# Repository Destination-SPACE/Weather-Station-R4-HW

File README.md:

# Destination Weather Station R4 - Hardware
Hardware repository for the Destination Weather Station R4 remote sensing platform

## Features
- Seeeduino XIAO SAMD21 M0 microcontroller
- BME280 environmental sensor
- 128x64 OLED display
- microSD card connector
- STEMMA-QT connector
- Sensor Hat mezzanine connectors (reversable)

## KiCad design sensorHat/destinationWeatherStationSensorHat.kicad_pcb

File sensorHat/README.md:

# Destination Weather Station Sensor Hat - Hardware
Hardware for the Destination Weather Station Sensor Hat environmental sensor expansion board

## Features
- SCD40 CO<sub>2</sub> sensor
- ENS160 VOC & eCO<sub>2</sub> sensor
- GUVA-S12SD UVA (350nm) sensor
- GUVB-S11SD UVB (300nm) sensor
- BH1750 ambient light sensor
- Weather Station mezzanine connectors (reversable)

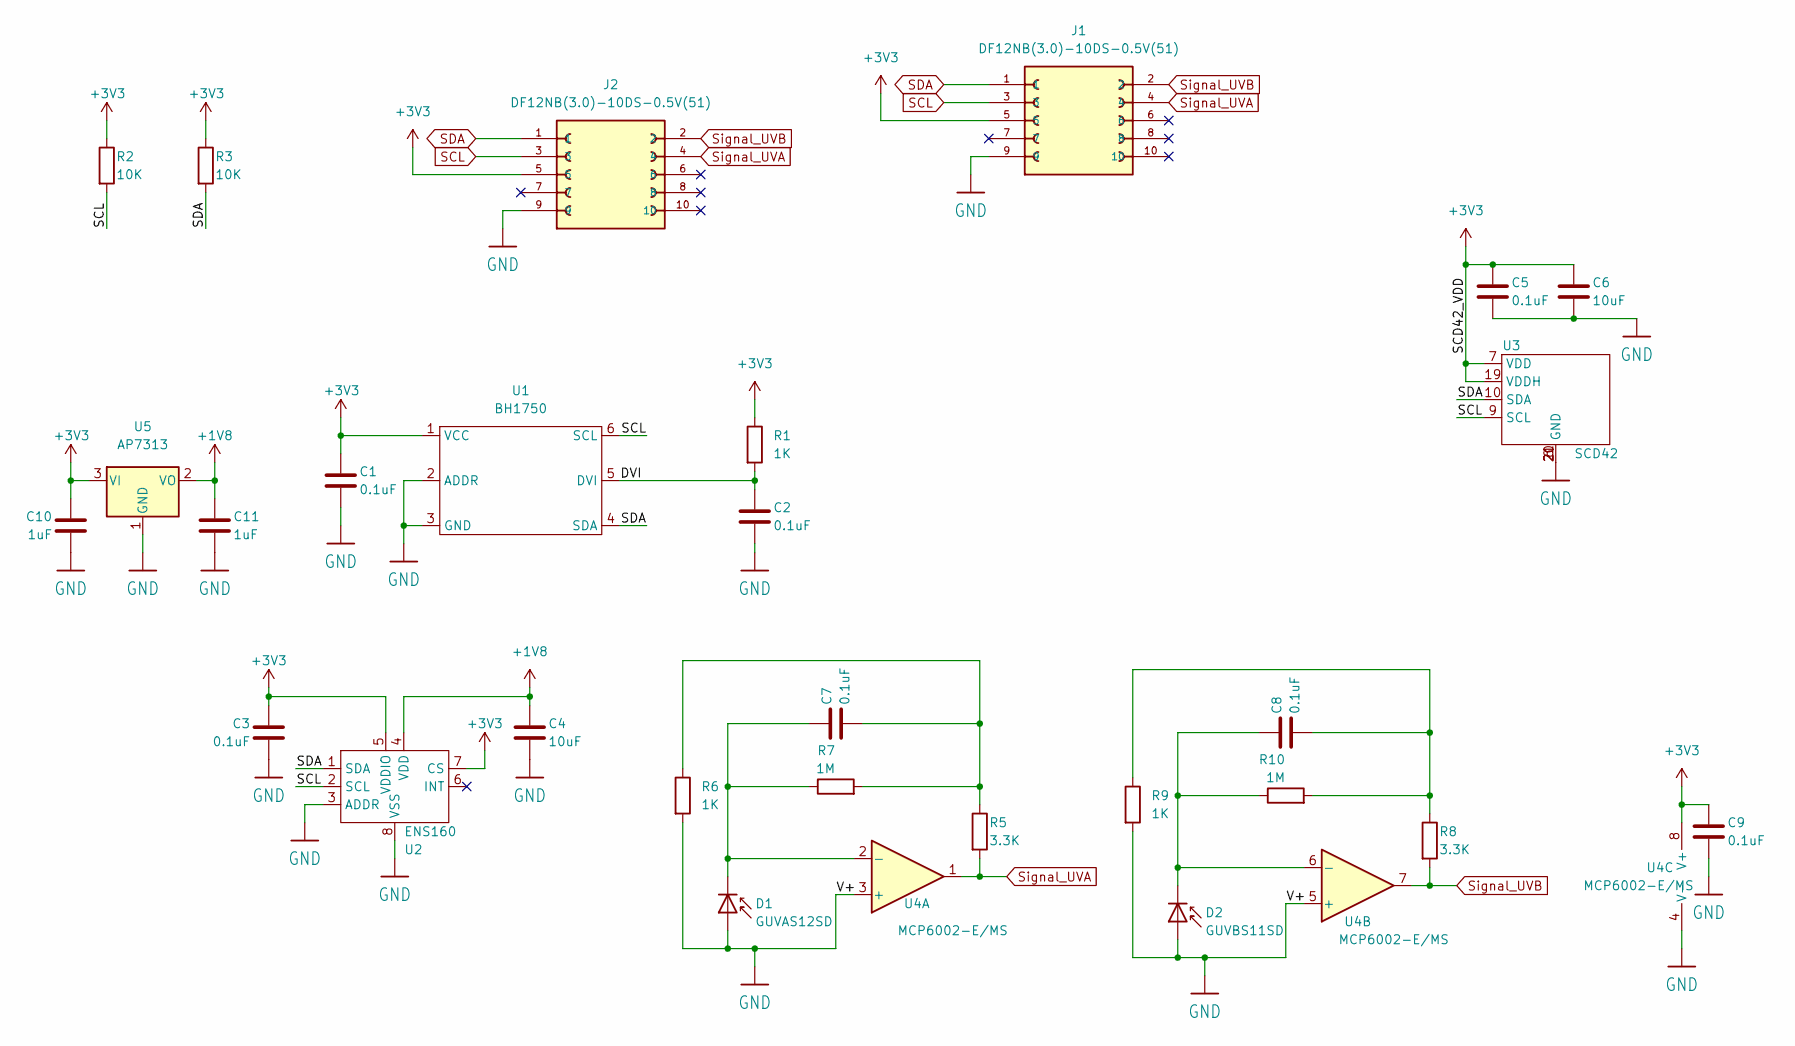
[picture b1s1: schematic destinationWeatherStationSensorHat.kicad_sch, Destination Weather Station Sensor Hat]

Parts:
C1, C2, C3, C5, C7, C8, C9: 0.1uF; C_0603_1608Metric; mpn CGA3E2X7R1E104K080AA
C4, C6: 10uF; C_0603_1608Metric; mpn C1608X5R1A106K080AC
C10, C11: 1uF; C_0603_1608Metric; mpn CGA3E1X7R1E105K080AC
D1: GUVAS12SD; mpn GUVA-S12SD
D2: GUVBS11SD; GUVAS12SD; mpn GUVB-S11SD
J1, J2: DF12NB(3.0)-10DS-0.5V(51); HRS_DF12NB(3.0)-10DS-0.5V(51); mpn DF12NB(3.0)-10DS-0.5V(51)
R1, R6, R9: 1K; R_0603_1608Metric; mpn CRCW06031K00FKEA
R2, R3: 10K; R_0603_1608Metric; mpn CRCW060310K0JNEB
R5, R8: 3.3K; R_0603_1608Metric; mpn CRCW06033K30FKEA
R7, R10: 1M; R_0603_1608Metric; mpn CRCW06031M00FKEA
U1: BH1750; XDCR_BH1750FVI-TR; mpn BH1750FVI-TR
U2: ENS160; LGA9CP105_3X3_300X300X90L70N; mpn ENS160-BGLM
U3: SCD42; SCD40; mpn SCD40-D-R2
U4: MCP6002-E/MS; MSOP-8_3x3mm_P0.65mm; mpn MCP6002-E/MS
U5: AP7313; AP7313-18SAG-7

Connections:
+1V8: C4.1, C11.1, U2.4 (VDD), U5.2 (VO)
+3V3: C1.1, C3.1, C5.1, C6.1, C9.1, C10.1, J1.5, J2.5, R1.1, R2.1, R3.1, U1.1 (VCC), U2.5 (VDDIO), U2.7 (CS), U3.7 (VDD), U3.19 (VDDH), U4.8 (V+), U5.3 (VI)
/DVI: C2.1, R1.2, U1.5 (DVI)
GND: C1.2, C2.2, C3.2, C4.2, C5.2, C6.2, C9.2, C10.2, C11.2, D1.2 (A), D2.2 (A), J1.9, J2.9, R6.2, R9.2, U1.2 (ADDR), U1.3 (GND), U2.3 (ADDR), U2.8 (VSS), U2.9 (VSS), U3.6 (GND), U3.20 (GND), U3.21 (GND), U4.3 (+), U4.4 (V-), U4.5 (+), U5.1 (GND)
unnamed: C7.1, D1.1 (K), R7.1, U4.2 (-)
unnamed: C7.2, R5.1, R6.1, R7.2
unnamed: C8.1, D2.1 (K), R10.1, U4.6 (-)
unnamed: C8.2, R8.1, R9.1, R10.2
SCL: J1.3, J2.3, R2.2, U1.6 (SCL), U2.2 (SCL), U3.9 (SCL)
SDA: J1.1, J2.1, R3.2, U1.4 (SDA), U2.1 (SDA), U3.10 (SDA)
Signal_UVA: J1.4, J2.4, R5.2, U4.1
Signal_UVB: J1.2, J2.2, R8.2, U4.7

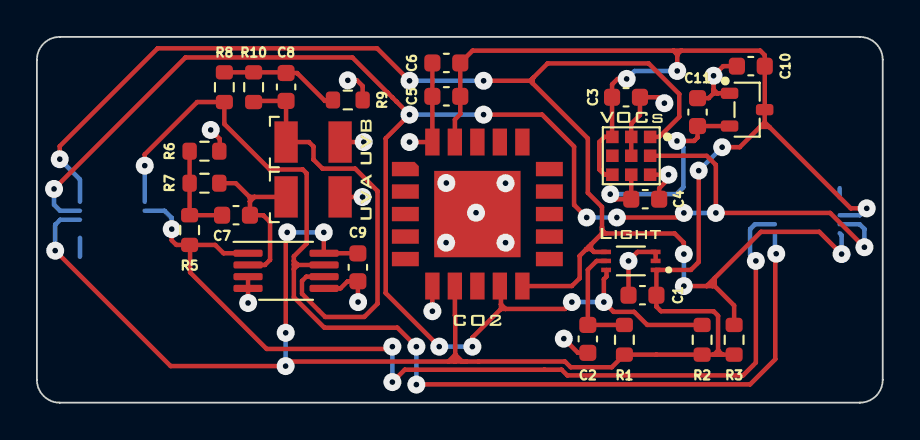
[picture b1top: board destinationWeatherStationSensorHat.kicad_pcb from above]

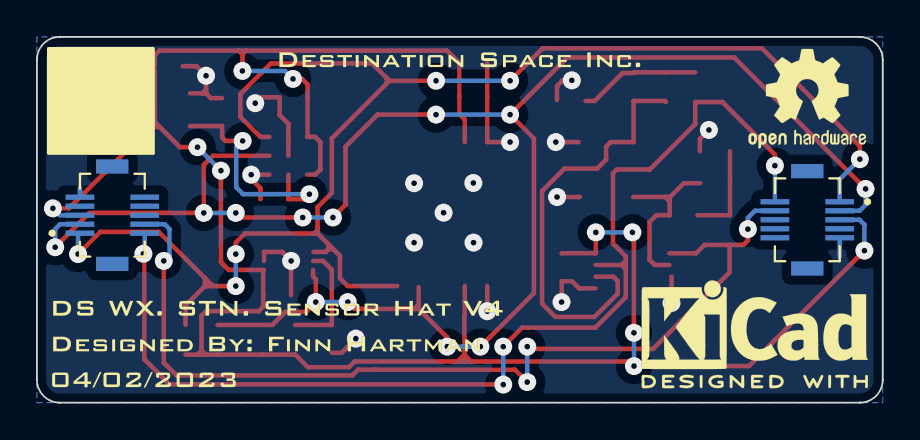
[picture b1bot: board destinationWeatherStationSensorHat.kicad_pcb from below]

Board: 2 copper layers, 47.0 x 20.3 mm, 36 parts (4 on the bottom side), 12 nets.

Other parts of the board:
kibuzzard-63A142C4: G***; kibuzzard-63A142C4
kibuzzard-63A142D7: G***; kibuzzard-63A142D7
kibuzzard-63A142F5: G***; kibuzzard-63A142F5
kibuzzard-63A14315: G***; kibuzzard-63A14315
kibuzzard-63A14339: G***; kibuzzard-63A14339
kibuzzard-641DA226: G***; kibuzzard-641DA226
kibuzzard-6429C003: G***; kibuzzard-6429C003

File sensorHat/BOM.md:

| Item | Qty | Reference(s)               | Value                     | Manufacturer           | mpn                       |
| ---- | --- | -------------------------- | ------------------------- | ---------------------- | ------------------------- |
| 1    | 7   | C1, C2, C3, C4, C7, C8, C9 | 0.1uF                     | TDK Corporation        | CGA3E2X7R1E104K080AA      |
| 2    | 1   | C5                         | 10uF                      | TDK Corportation       | C1608X5R1A106K080AC       |
| 3    | 1   | D1                         | GUVAS12SD                 | Genicom Co., Ltd.      | GUVA-S12SD                |
| 4    | 1   | D2                         | GUVBS11SD                 | Genicom Co., Ltd.      | GUVB-S11SD                |
| 5    | 2   | J1, J2                     | DF12NB(3.0)-10DS-0.5V(51) | Hirose Electric Co Ltd | DF12NB(3.0)-10DS-0.5V(51) |
| 6    | 3   | R1, R6, R9                 | 1K                        | Vishay Dale            | CRCW06031K00FKEA          |
| 7    | 2   | R2, R3                     | 10K                       | Vishay Dale            | CRCW060310K0JNEB          |
| 8    | 1   | R4                         | 4.7R                      | Vishay Dale            | CRCW06034R70JNEA          |
| 9    | 2   | R5, R8                     | 3.3K                      | Vishay Dale            | CRCW06033K30FKEA          |
| 10   | 2   | R7, R10                    | 1M                        | Vishay Dale            | CRCW06031M00FKEA          |
| 11   | 1   | U1                         | BH1750                    | Rohm Semiconductor     | BH1750FVI-TR              |
| 12   | 1   | U2                         | SGP40                     | Sensirion AG           | SGP40-D-R4                |
| 13   | 1   | U3                         | SCD42                     | Sensirion AG           | SCD40-D-R2                |
| 14   | 1   | U4                         | MCP6002-E/MS              | Microchip Technology   | MCP6002-E/MS              |

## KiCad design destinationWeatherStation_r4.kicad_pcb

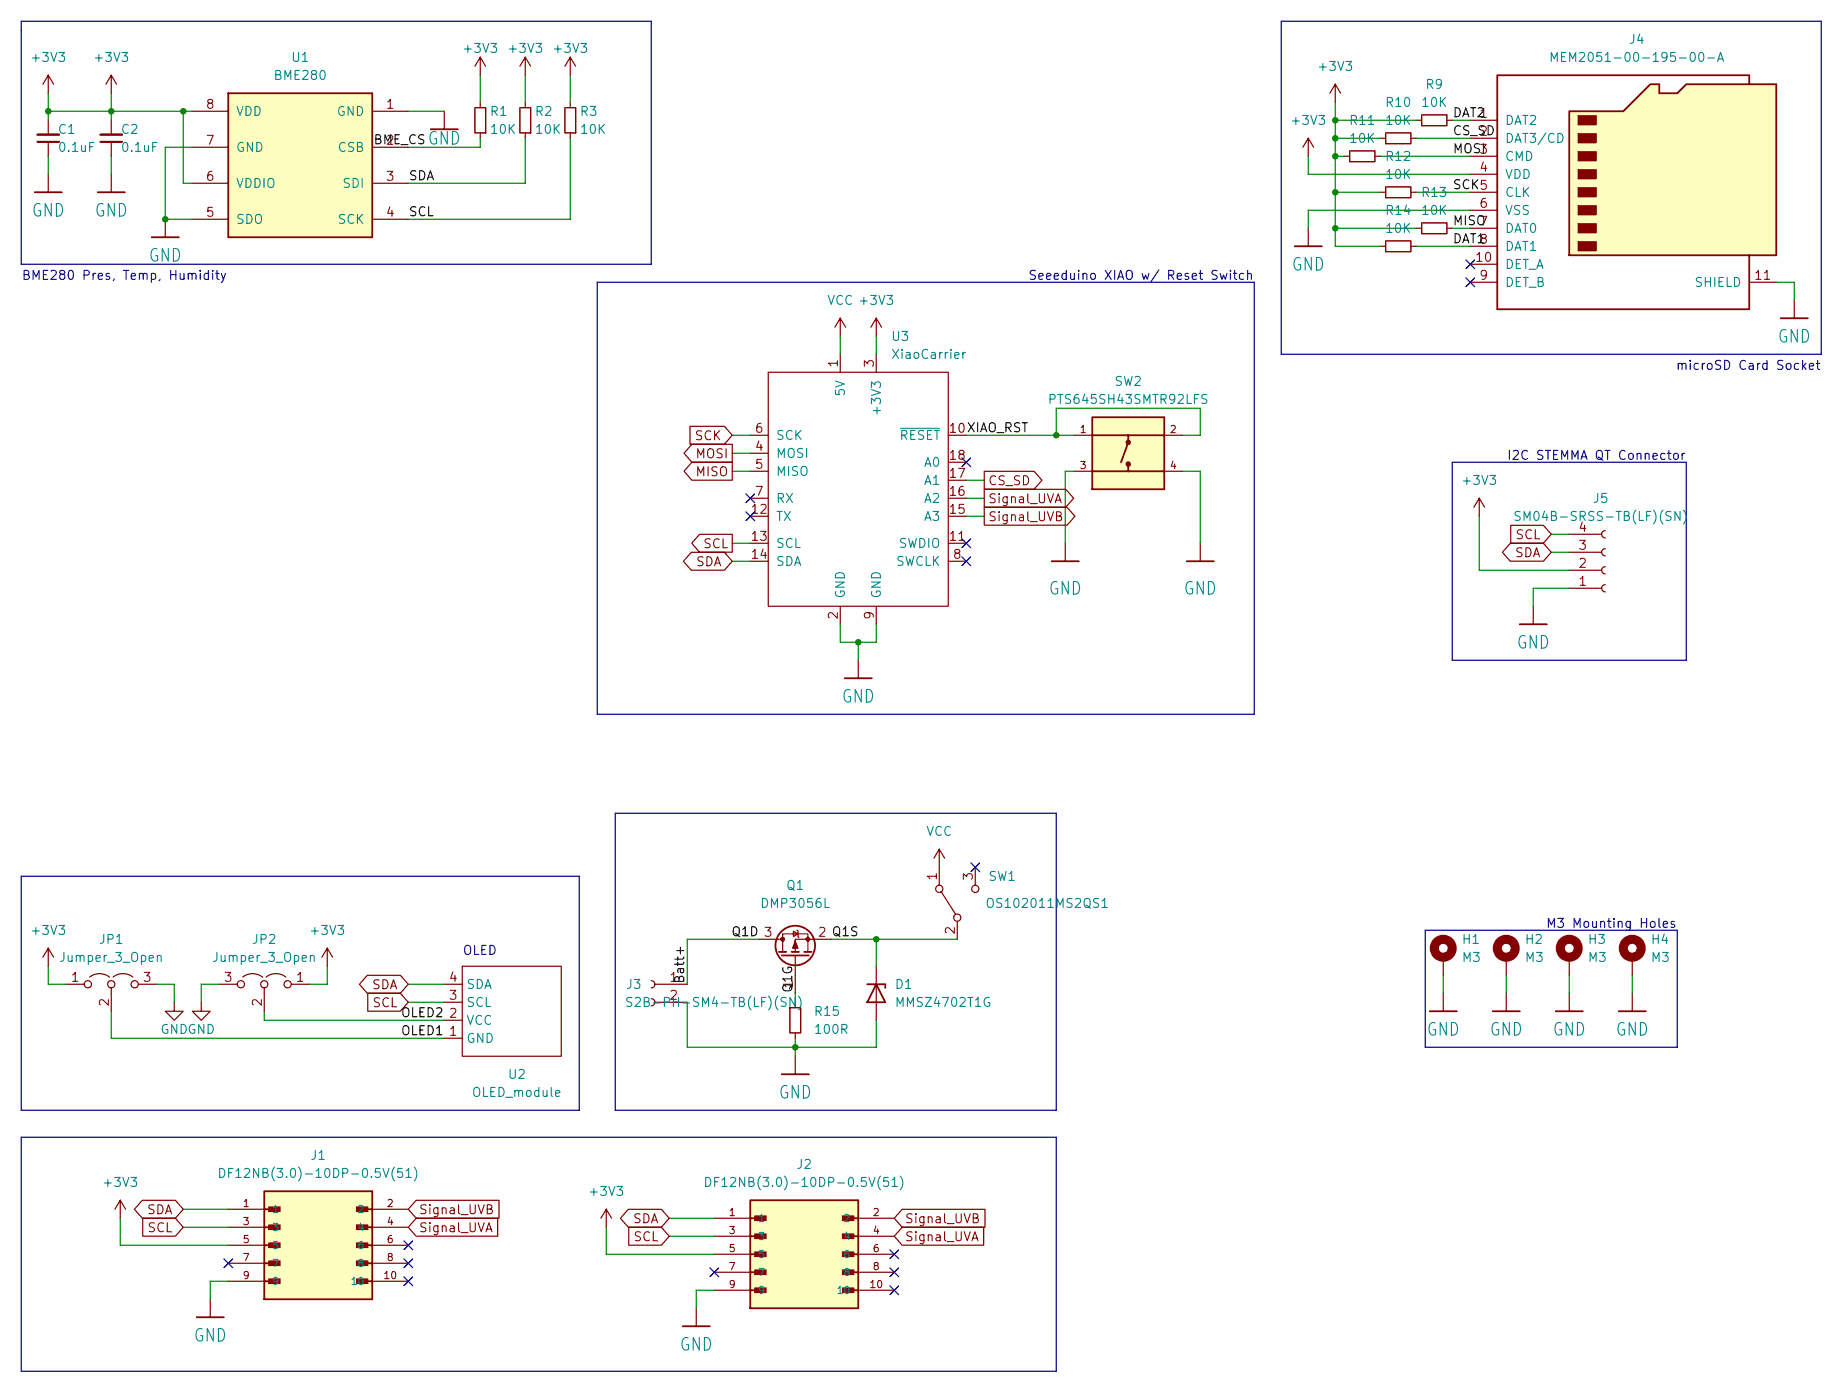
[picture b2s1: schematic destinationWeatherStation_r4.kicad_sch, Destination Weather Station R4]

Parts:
C1, C2: 0.1uF; C_0603_1608Metric; mpn CGA3E2X7R1E104K080AA
D1: MMSZ4702T1G; D_SOD-123; mpn MMSZ4702T1G
H1, H2, H3, H4: M3; MountingHole_3.2mm_M3_DIN965_Pad
J1, J2: DF12NB(3.0)-10DP-0.5V(51); HRS_DF12NB(3.0)-10DP-0.5V(51); mpn DF12NB(3.0)-10DP-0.5V(51)
J3: S2B-PH-SM4-TB(LF)(SN); JST_PH_S2B-PH-SM4-TB_1x02-1MP_P2.00mm_Horizontal; mpn S2B-PH-SM4-TB(LF)(SN)
J4: MEM2051-00-195-00-A; MF_Connectors-MF-MICROSD; mpn MEM2051-00-195-00-A
J5: SM04B-SRSS-TB(LF)(SN); JST_SH_SM04B-SRSS-TB_1x04-1MP_P1.00mm_Horizontal; mpn SM04B-SRSS-TB(LF)(SN)
JP1, JP2: Jumper_3_Open; SolderJumper-3_P1.3mm_Open_RoundedPad1.0x1.5mm
Q1: DMP3056L; SOT-23; mpn DMP3056L-7
R1, R2, R3, R9, R10, R11, R12, R13, R14: 10K; R_0603_1608Metric; mpn CRCW060310K0JNEB
R15: 100R; R_0603_1608Metric; mpn CRCW0603100RFKEA
SW1: OS102011MS2QS1; SW_SPDT; mpn OS102011MS2QS1
SW2: PTS645SH43SMTR92LFS; MF_Switches-TACT6MM; mpn PTS645SH43SMTR92LFS
U1: BME280; Bosch_LGA-8_2.5x2.5mm_P0.65mm_ClockwisePinNumbering; mpn BME280
U2: OLED_module
U3: XiaoCarrier; mpn 102010328

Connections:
+3V3: C1.2, C2.2, J1.5, J2.5, J4.4 (VDD), J5.2, JP1.1 (A), JP2.1 (A), R1.2, R2.2, R3.2, R9.1, R10.1, R11.1, R12.1, R13.1, R14.1, U1.6 (VDDIO), U1.8 (VDD), U3.3 (+3V3)
/BME_CS: R1.1, U1.2 (CSB)
/Batt+: J3.1, Q1.3 (D)
/DAT1: J4.8 (DAT1), R14.2
/DAT2: J4.1 (DAT2), R9.2
/OLED1: JP1.2 (C), U2.1 (GND)
/OLED2: JP2.2 (C), U2.2 (VCC)
/Q1G: Q1.1 (G), R15.1
/Q1S: D1.1 (K), Q1.2 (S), SW1.2 (B)
/XIAO_RST: SW2.1, SW2.2, U3.10 (~RESET)
CS_SD: J4.2 (DAT3/CD), R10.2, U3.17 (A1)
GND: C1.1, C2.1, D1.2 (A), H1.1, H2.1, H3.1, H4.1, J1.9, J2.9, J3.2, J4.6 (VSS), J4.11 (SHIELD), J5.1, JP1.3 (B), JP2.3 (B), R15.2, SW2.3, SW2.4, U1.1 (GND), U1.5 (SDO), U1.7 (GND), U3.2 (GND), U3.9 (GND)
MISO: J4.7 (DAT0), R13.2, U3.5 (MISO)
MOSI: J4.3 (CMD), R11.2, U3.4 (MOSI)
SCK: J4.5 (CLK), R12.2, U3.6 (SCK)
SCL: J1.3, J2.3, J5.4, R3.1, U1.4 (SCK), U2.3 (SCL), U3.13 (SCL)
SDA: J1.1, J2.1, J5.3, R2.1, U1.3 (SDI), U2.4 (SDA), U3.14 (SDA)
Signal_UVA: J1.4, J2.4, U3.16 (A2)
Signal_UVB: J1.2, J2.2, U3.15 (A3)
VCC: SW1.1 (A), U3.1 (5V)

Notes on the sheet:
I2C STEMMA QT Connector
BME280 Pres, Temp, Humidity
OLED
Seeeduino XIAO w/ Reset Switch
M3 Mounting Holes
microSD Card Socket

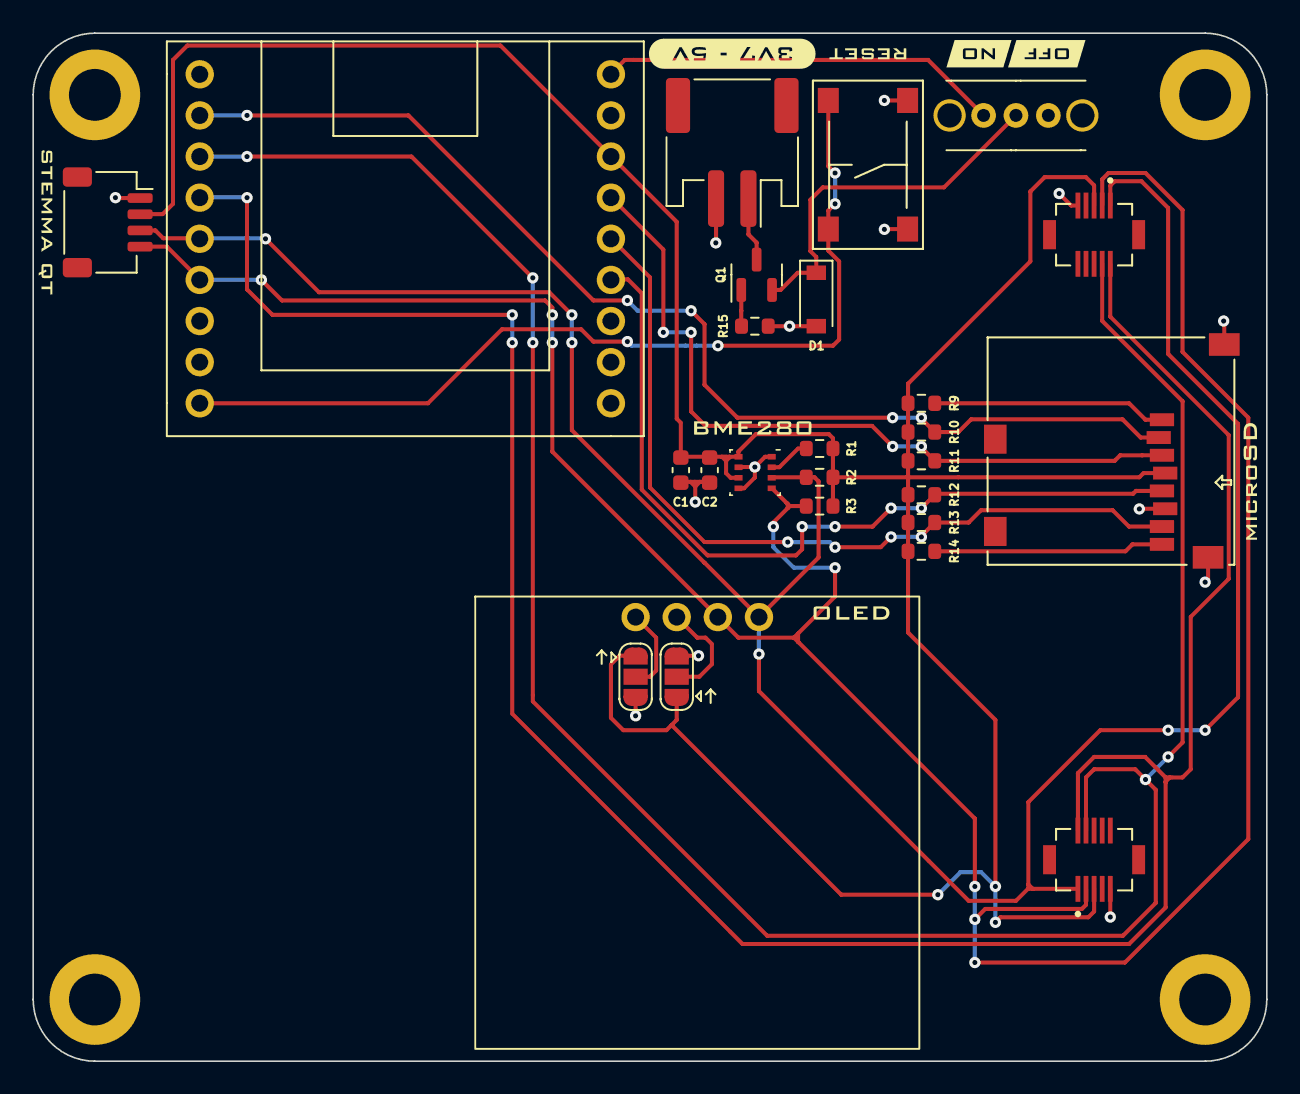
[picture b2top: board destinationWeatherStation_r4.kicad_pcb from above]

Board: 2 copper layers, 76.2 x 63.5 mm, 39 parts (1 on the bottom side), 20 nets.

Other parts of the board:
kibuzzard-63A143BA: G***; kibuzzard-63A143BA
kibuzzard-63A146BA: G***; kibuzzard-63A146BA
kibuzzard-63A147A6: G***; kibuzzard-63A147A6
kibuzzard-63A1452B: G***; kibuzzard-63A1452B
kibuzzard-63A14452: G***; kibuzzard-63A14452
kibuzzard-63A14586: G***; kibuzzard-63A14586
kibuzzard-6429C5F6: G***; kibuzzard-6429C5F6
kibuzzard-64039D9C: G***; kibuzzard-64039D9C
kibuzzard-64039D84: G***; kibuzzard-64039D84

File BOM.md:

| Item | Qty | Reference(s)                            | Value                     | Manufacturer              | mpn                       |
| ---- | --- | --------------------------------------- | ------------------------- | ------------------------- | ------------------------- |
| 1    | 2   | C1, C2                                  | 0.1uF                     | TDK Corporation           | CGA3E2X7R1E104K080AA      |
| 2    | 1   | D1                                      | MMSZ4702T1G               | Onsemi                    | MMSZ4702T1G               |
| 4    | 2   | J1, J2                                  | DF12NB(3.0)-10DP-0.5V(51) | Hirose Electric Co Ltd    | DF12NB(3.0)-10DP-0.5V(51) |
| 5    | 1   | J3                                      | S2B-PH-SM4-TB(LF)(SN)     | JST Sales America Inc.    | S2B-PH-SM4-TB(LF)(SN)     |
| 6    | 1   | J4                                      | MEM2051-00-195-00-A       | GCT                       | MEM2051-00-195-00-A       |
| 7    | 1   | J5                                      | SM04B-SRSS-TB(LF)(SN)     | JST Sales America Inc.    | SM04B-SRSS-TB(LF)(SN)     |
| 9    | 1   | Q1                                      | DMP3056L                  | Diodes Incorporated       | DMP3056L-7                |
| 10   | 9   | R1, R2, R3, R9, R10, R11, R12, R13, R14 | 10K                       | Vishay Dale               | CRCW060310K0JNEB          |
| 11   | 1   | R15                                     | 100R                      | Vishay Dale               | CRCW0603100RFKEA          |
| 12   | 1   | SW1                                     | OS102011MS2QS1            | C&K                       | OS102011MS2QS1            |
| 13   | 1   | SW2                                     | PTS645SH43SMTR92LFS       | C&K                       | PTS645SH43SMTR92LFS       |
| 14   | 1   | U1                                      | BME280                    | Bosch Sensortec           | BME280                    |
| 15   | 1   | U2                                      | OLED module               | Frienda                   | B08VNNCLHD                |
| 16   | 1   | U3                                      | Xiao Carrier              | Seeed Technology Co., Ltd | 102010328                 |

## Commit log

2023-04-09 Create LICENCE
2023-04-09 Update LICENCE
2023-04-09 Create LICENSE
